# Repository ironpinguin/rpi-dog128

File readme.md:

# Software to connect a DOGL128-6 LCD to a Raspberry Pi

## Requirements

[wiringPi ](http://wiringpi.com/) Library is required.
Software must run with root user!

To test the results of your render codee locally, use the emu package.

## Hardware

coming soon.

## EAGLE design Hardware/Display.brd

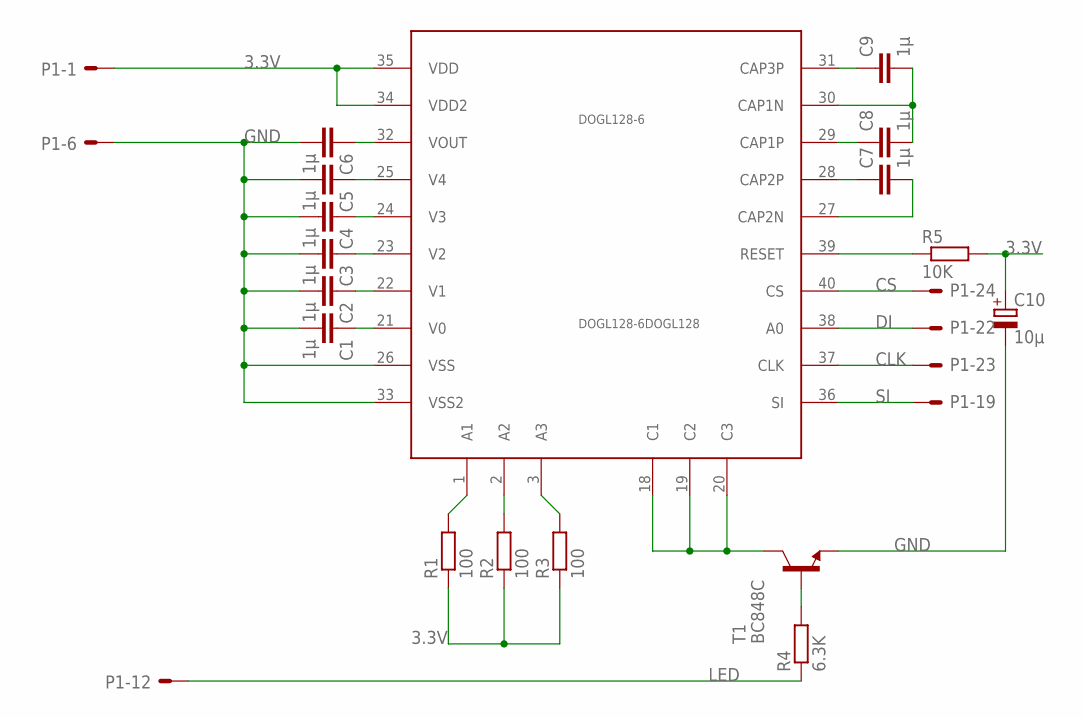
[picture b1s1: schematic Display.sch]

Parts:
C1, C2, C3, C4, C5, C6, C7, C8, C9: 1µ; C1206
C10: 10µ; CT6032
DOGL128-6: DOGL128-6DOGL128; DOGL128
P1: ML26E; ML26
R1, R2, R3: 100; 0207/10
R4: 6.3K; 0207/10
R5: 10K; 0207/12
T1: BC848C; SOT23-BEC

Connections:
3.3V: C10.+, DOGL128-6.34 (VDD2), DOGL128-6.35 (VDD), P1.1, R1.1, R2.1, R3.1, R5.2
CLK: DOGL128-6.37 (CLK), P1.23
CS: DOGL128-6.40 (CS), P1.24
DI: DOGL128-6.38 (A0), P1.22
GND: C1.2, C2.2, C3.2, C4.2, C5.2, C6.2, C10.-, DOGL128-6.26 (VSS), DOGL128-6.33 (VSS2), P1.6, T1.E
LED: P1.12, R4.1
unnamed: C6.1, DOGL128-6.32 (VOUT)
unnamed: C5.1, DOGL128-6.25 (V4)
unnamed: C4.1, DOGL128-6.24 (V3)
unnamed: C3.1, DOGL128-6.23 (V2)
unnamed: C2.1, DOGL128-6.22 (V1)
unnamed: C1.1, DOGL128-6.21 (V0)
unnamed: C7.1, DOGL128-6.28 (CAP2P)
unnamed: C8.1, DOGL128-6.29 (CAP1P)
unnamed: C9.1, DOGL128-6.31 (CAP3P)
unnamed: C8.2, C9.2, DOGL128-6.30 (CAP1N)
unnamed: C7.2, DOGL128-6.27 (CAP2N)
unnamed: DOGL128-6.1 (A1), R1.2
unnamed: DOGL128-6.2 (A2), R2.2
unnamed: DOGL128-6.3 (A3), R3.2
unnamed: DOGL128-6.18 (C1), DOGL128-6.19 (C2), DOGL128-6.20 (C3), T1.C
unnamed: R4.2, T1.B
unnamed: DOGL128-6.39 (RESET), R5.1
SI: DOGL128-6.36 (SI), P1.19

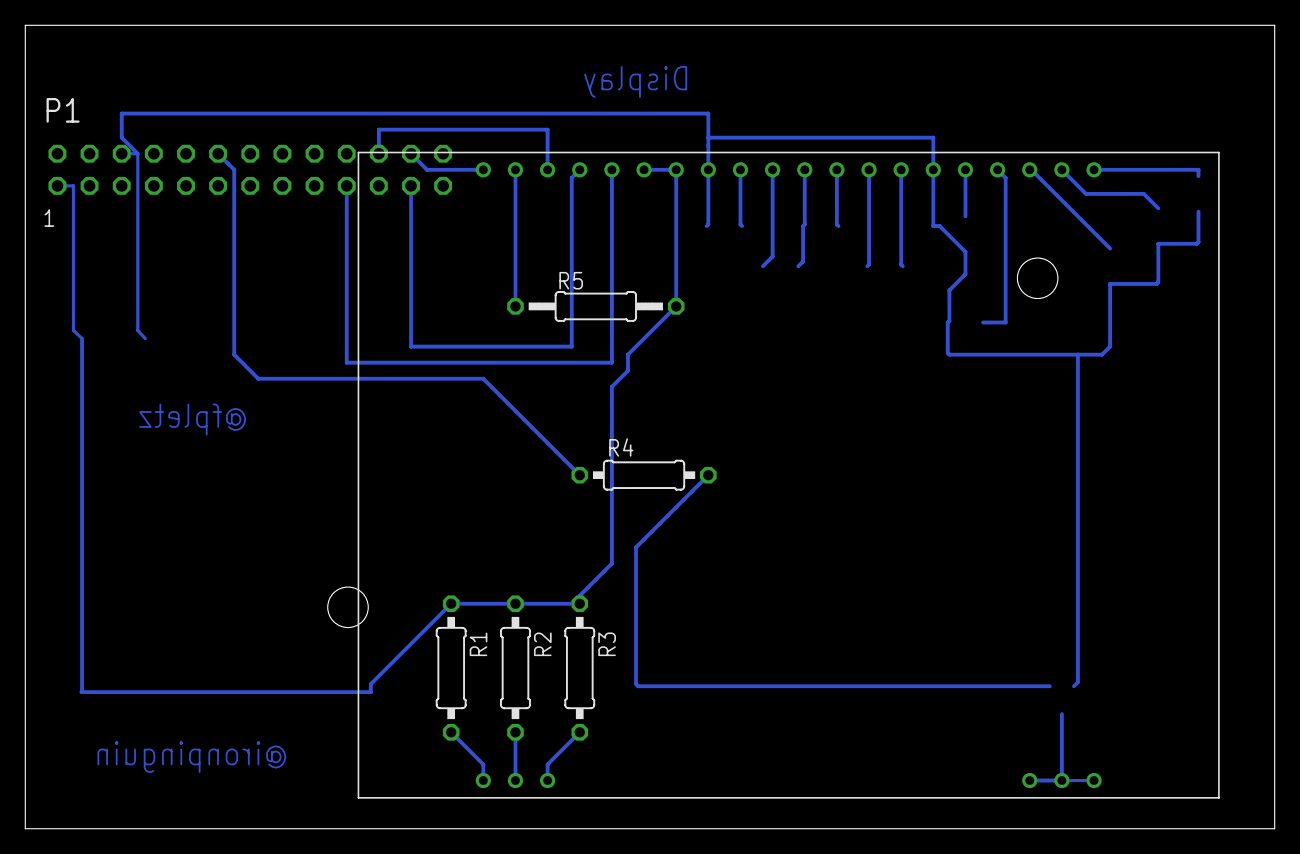
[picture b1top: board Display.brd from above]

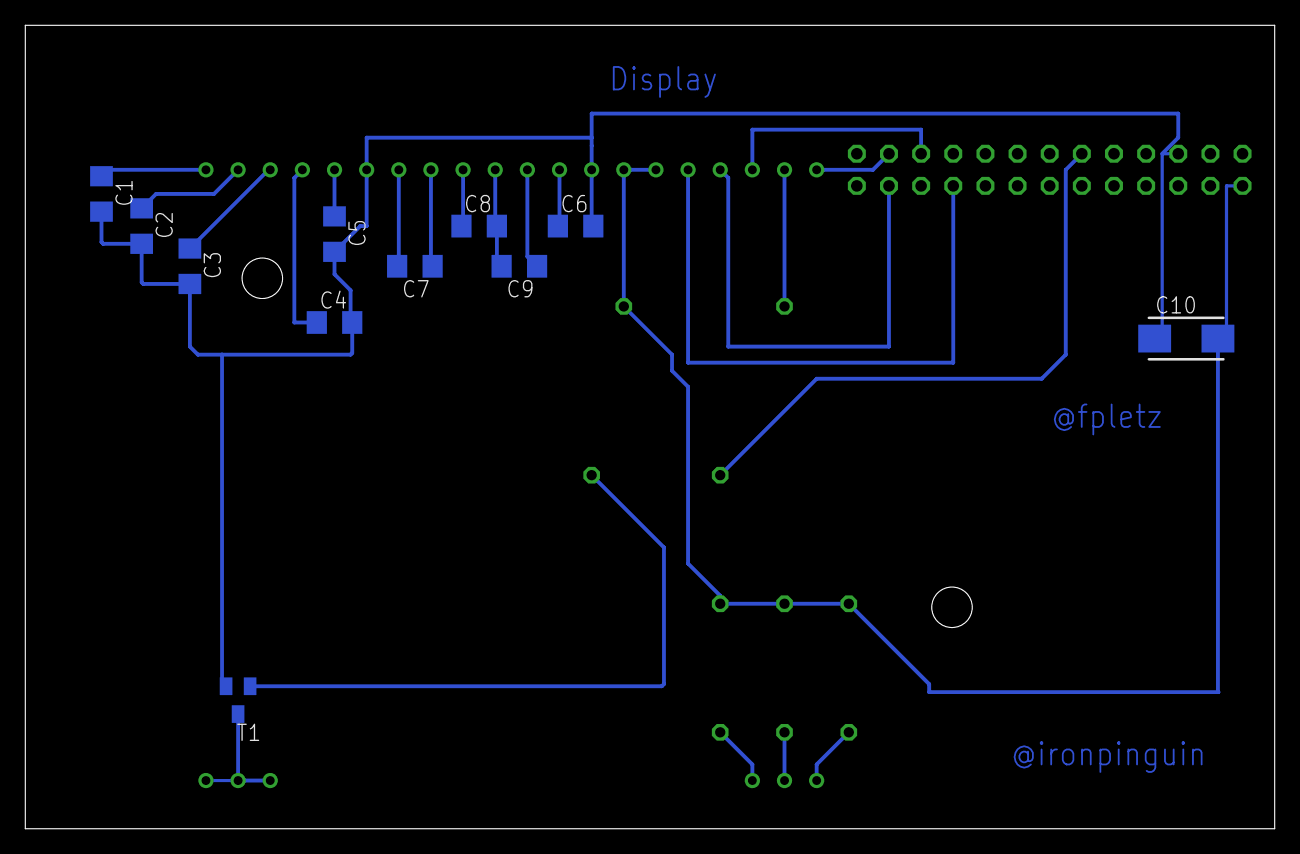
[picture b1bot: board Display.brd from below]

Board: 2 copper layers, 98.7 x 63.5 mm, 18 parts (11 on the bottom side), 24 nets.

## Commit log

2013-09-18 initial code
2013-09-18 first write pixel from display puffer to lcd.
2013-09-21 basis implementation for using fonts.
2013-09-21 initial add more font sizes.
2013-09-21 add readme
2013-09-21 typo in readme
2013-09-21 Multifonts prepare.
2013-09-21 get working the most fonts. Problems with 10x16-12x20 :-(
2013-09-22 Added stub for emu package. Extended readme.
2013-09-22 add wiringPi submodule
2013-09-22 Refactoring for more modularity needed for emulator, step 1.
2013-09-22 Corrected typo
2013-09-23 Refactoring to increase modularity for emulator step 2. Emulator displays fonts.
2013-09-23 fix mock and clean dogl.c
2013-09-23 fix merge
2013-09-23 Adapted display style a little bit.
2013-09-23 get working emu on mac osx
2013-10-06 prepare for convert to a library.
2013-10-06 first step to make a library
2013-10-06 first running version with library
2013-10-06 workaround for mac.
2013-10-11 Fixed 10x16 fonts (with example).
2013-10-11 Added basis for selecting arbitrary fonts at runtime.
2013-10-11 Added forgotten files for arbitrary font selection commit.
2013-10-11 Added remaining fonts.
2013-10-14 fix example and library header for new method initFonts.
2013-10-14 add method to setup display.
2013-10-15 add circle draw.
2013-10-17 implement circle. add logging screen to display with mock.
2013-10-17 make mock console output readable.
2013-10-24 Prepare testing enviroment.
2013-10-25 fix build on raspberryPi
2013-10-25 Fixed C99 mode in makefiles.
2013-10-25 Added font loading
2013-10-25 ignore files
2013-10-25 remove no more used hardware reset!
2013-10-25 Add install and uninstall function.
2013-10-27 get more brightness.
2013-11-06 Add Hardware Design
2013-11-08 remove not needed casts.
2013-11-13 ignore .so files
2013-11-22 Added architecture and make scripts for GL-Mock. Added fork logic.
2013-11-22 GLMock working (without proper cleanup!), removed outdated emu folder.
2013-11-29 fix building static lib.
2013-12-22 add license
2013-12-22 Add png version of schema and circuit layout
2014-01-11 fix writing the display.log file.
2014-01-11 fix make of mock's
2014-01-11 Fix Makefiles. Define use of gnu methods.
2014-01-11 Fix example make
2014-01-11 add wiringPiISR to mock for interrupt handling.
2014-01-12 add pullUpDnControl to mock
2014-01-12 fix style.
2014-01-18 Fix segfault with to long big text
2014-01-19 fix position check
2014-01-19 add install and uninstall to global Makefile
2014-01-19 Fix screen
2014-01-26 make header file to prevent duplicate coding for the two mock versions.
2014-03-10 more mac compatibility.
2014-03-12 fix some misstake
